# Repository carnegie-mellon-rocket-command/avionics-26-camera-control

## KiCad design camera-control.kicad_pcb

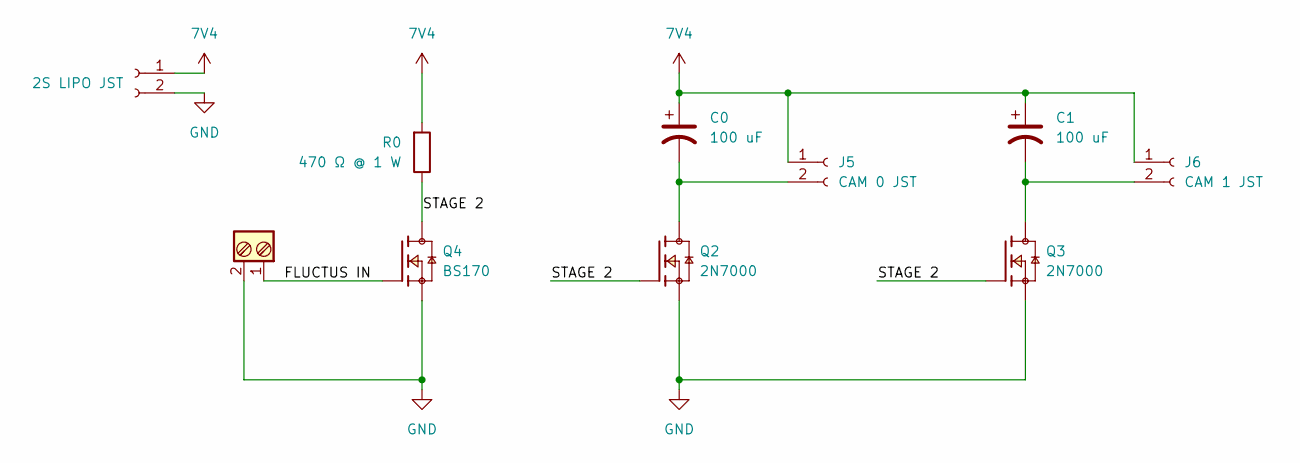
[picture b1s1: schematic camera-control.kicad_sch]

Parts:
C0, C1: 100 uF; CP_Radial_D7.5mm_P2.50mm
J2: Screw_Terminal_2_P2.54mm; TerminalBlock_Phoenix_MPT-0,5-2-2.54_1x02_P2.54mm_Horizontal
J4: 2S LIPO JST; JST_EH_B2B-EH-A_1x02_P2.50mm_Vertical
J5: CAM 0 JST; JST_EH_B2B-EH-A_1x02_P2.50mm_Vertical
J6: CAM 1 JST; JST_EH_B2B-EH-A_1x02_P2.50mm_Vertical
Q2, Q3: 2N7000; TO-92_HandSolder; PARTREV 2024-07-16
Q4: BS170; TO-92_HandSolder; PARTREV 2024-07-16
R0: 470 Ω @ 1 W; R_Axial_DIN0414_L11.9mm_D4.5mm_P15.24mm_Horizontal

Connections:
7V4: C0.1, C1.1, J4.1, J5.1, J6.1, R0.2
/FLUCTUS IN: J2.1, Q4.2
/STAGE 2: Q2.2, Q3.2, Q4.3, R0.1
GND: J2.2, J4.2, Q2.1, Q3.1, Q4.1
unnamed: C0.2, J5.2, Q2.3
unnamed: C1.2, J6.2, Q3.3

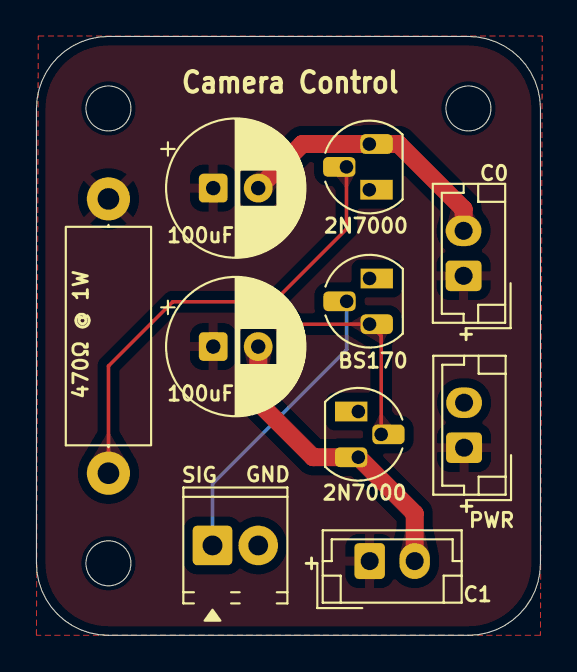
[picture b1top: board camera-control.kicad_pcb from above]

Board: 2 copper layers, 28.0 x 33.3 mm, 11 parts (1 on the bottom side), 6 nets.

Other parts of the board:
svg2mod: G***; logo

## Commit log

2026-01-30 init
